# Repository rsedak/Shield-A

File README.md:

Introduction
============

Shield-A is Arduino Uno based shield for student education compatible with BASCOM-AVR(C) and Arduino IDE.
During programming please keep in mind next design rules:
- D0-D7 — LEDs can be used only if D12 is set to OUTPUT HIGH state
- LCD 1602 — can be used only if A3 is set to OUTPUT HIGH state
- RGB LED — are connected in matrix (D5-D7 - colors; D8-D11 - LEDs)
- D12 — enables D0-D7 LEDs
- D13 — reserved for buzzer
- A0 — reserved for potentiometer
- A1,A2 — reserved for switch in INPUT_PULLUP mode
- A3 — enables LCD 1602 back-light
- A4,A5 — reserved for I2C communication with on board pull-up resistors

Contributors
------------
- Petar Jurković — an initial idea for the educational shield with a list of features, QA test.
- Vladimir Mitrović — features, BASCOM-AVR expertise, schematic design
- Robert Sedak — features, Arduino expertise, schematic design, CAD design. 

Application
-----------
Robert Sedak made a video with examples programmed in Arduino IDE:

You can download examples from [here](examples/). 
Examples which name ends with '_R' are solution with register maniputalion.

Bill Of Materials
-----------------
- 1 ea., PCB from [PCBway.com](https://www.pcbway.com/project/shareproject/Shield_A_for_Arduino_Uno.html)
- 9 ea., 1K ohm 1/4W 1% Resistor (R1-R8, R13)
- 2 ea., 100 ohm 1/4W 1% Resistor (R9, R10)
- 2 ea., 560 ohm 1/4W 1% Resistor (R11-R12)
- 4 ea., 10K ohm 1/4W 1% Resistor (R14, R15, R17, R18)
- 2 ea., 18.2 ohm 1/4W 1% Resistor (R16)
- 8 ea., LED 3mm (D0-D7)
- 4 ea., RGB LED 5mm common Katode (D8-D11)
- 1 ea., 14x7.5mm passive electronic piezoelectric buzzer SE
- 2 ea., MOSFET BS170
- 1 ea., 3386-P 10K potentiometer with knob
- 1 ea., RV09 10K potentiometer - long shaft
- 1 ea., 2.54mm pitch slide DIP switch 2-bit
- 1 ea., 6x6x4.3mm SPST Momentary push switch
- 2 ea., 6x6x10mm SPST Momentary push switch
- 1 ea., 1x16Pin 2.54mm Straight Pin Header - Black
- 1 ea., 1x10Pin 2.54mm Straight Pin Header - Black
- 2 ea., 1x8Pin 2.54mm Straight Pin Header - Black
- 1 ea., 1x6Pin 2.54mm Straight Pin Header - Black
- 1 ea., 1x4 pin 2.54mm Socket Connector
- 1 ea., 1x16 pin 2.54mm Socket Connector
- 1 ea., LCD 1602 HD44780 (pin 15 is anode, pin 16 is katode)

Design Files
------------
This project is designed using Open Source [KiCad](http://kicad-pcb.org/). Design files are located in the [design_files](design_files/) folder.  You can see the [schematic](images/shield-a_schematic.png).

Gerber files
------------
You can download gerber files from [here](gerber/shield_a_v1.1.zip).

Firmware
--------
This project can be programmed using the Open Source [Arduino](https://www.arduino.cc/) and [BASCOM-AVR(C)](https://www.mcselec.com/index.php?option=com_content&task=view&id=14&Itemid=103).
Arduino examples are located in [examples](examples/) folder.

Assembly Instructions
---------------------
TBD

License
-------
[Attribution-ShareAlike 4.0 International (CC BY-SA 4.0)](https://creativecommons.org/licenses/by-sa/4.0/)

You are free to:
- Share — copy and redistribute the material in any medium or format
- Adapt — remix, transform, and build upon the material

This license is acceptable for Free Cultural Works.
- The licensor cannot revoke these freedoms as long as you follow the license terms.

Under the following terms:
- Attribution — You must give appropriate credit, provide a link to the license, and indicate if changes were made. You may do so in any reasonable manner, but not in any way that suggests the licensor endorses you or your use.
- ShareAlike — If you remix, transform, or build upon the material, you must distribute your contributions under the same license as the original.

No additional restrictions — You may not apply legal terms or technological measures that legally restrict others from doing anything the license permits.

Reference Designs ARE PROVIDED "AS IS" AND "WITH ALL FAULTS". Authors DISCLAIMS ALL OTHER WARRANTIES, EXPRESS OR IMPLIED, REGARDING PRODUCTS, INCLUDING BUT NOT LIMITED TO, ANY IMPLIED WARRANTIES OF MERCHANTABILITY OR FITNESS FOR A PARTICULAR PURPOSE.
Authors may make changes to specifications and product descriptions at any time, without notice. The Customer must notrely on the absence or characteristics of any features or instructions marked "reserved" or "undefined." 
Authors reservesthese for future definition and shall have no responsibility whatsoever for conflicts or incompatibilities arising from future changes to them. The product information on the Web Site or Materials is subject to change without notice. Do not finalize a design with this info.

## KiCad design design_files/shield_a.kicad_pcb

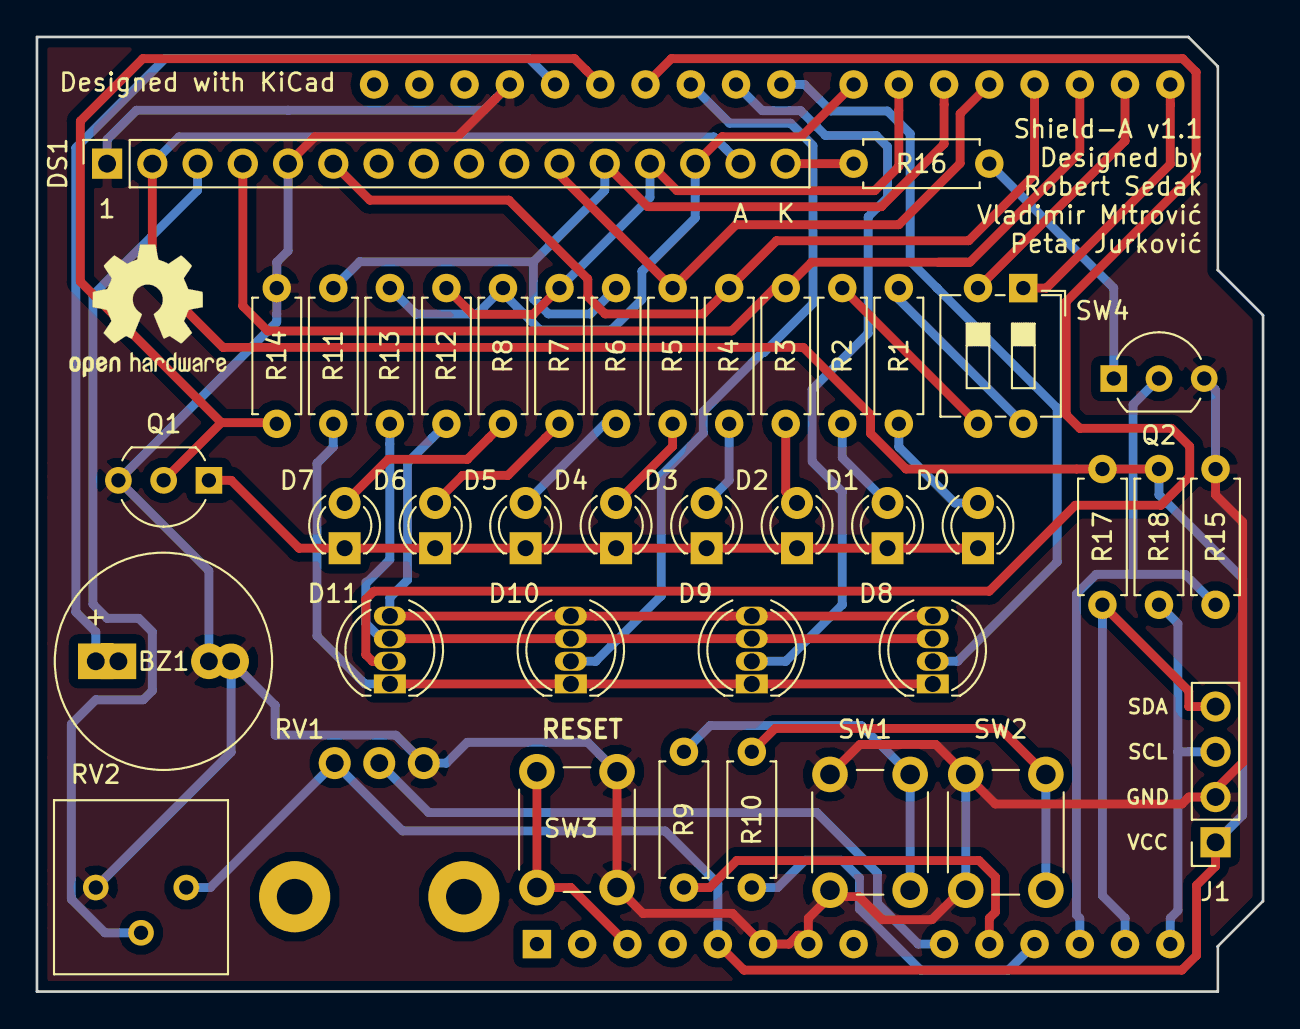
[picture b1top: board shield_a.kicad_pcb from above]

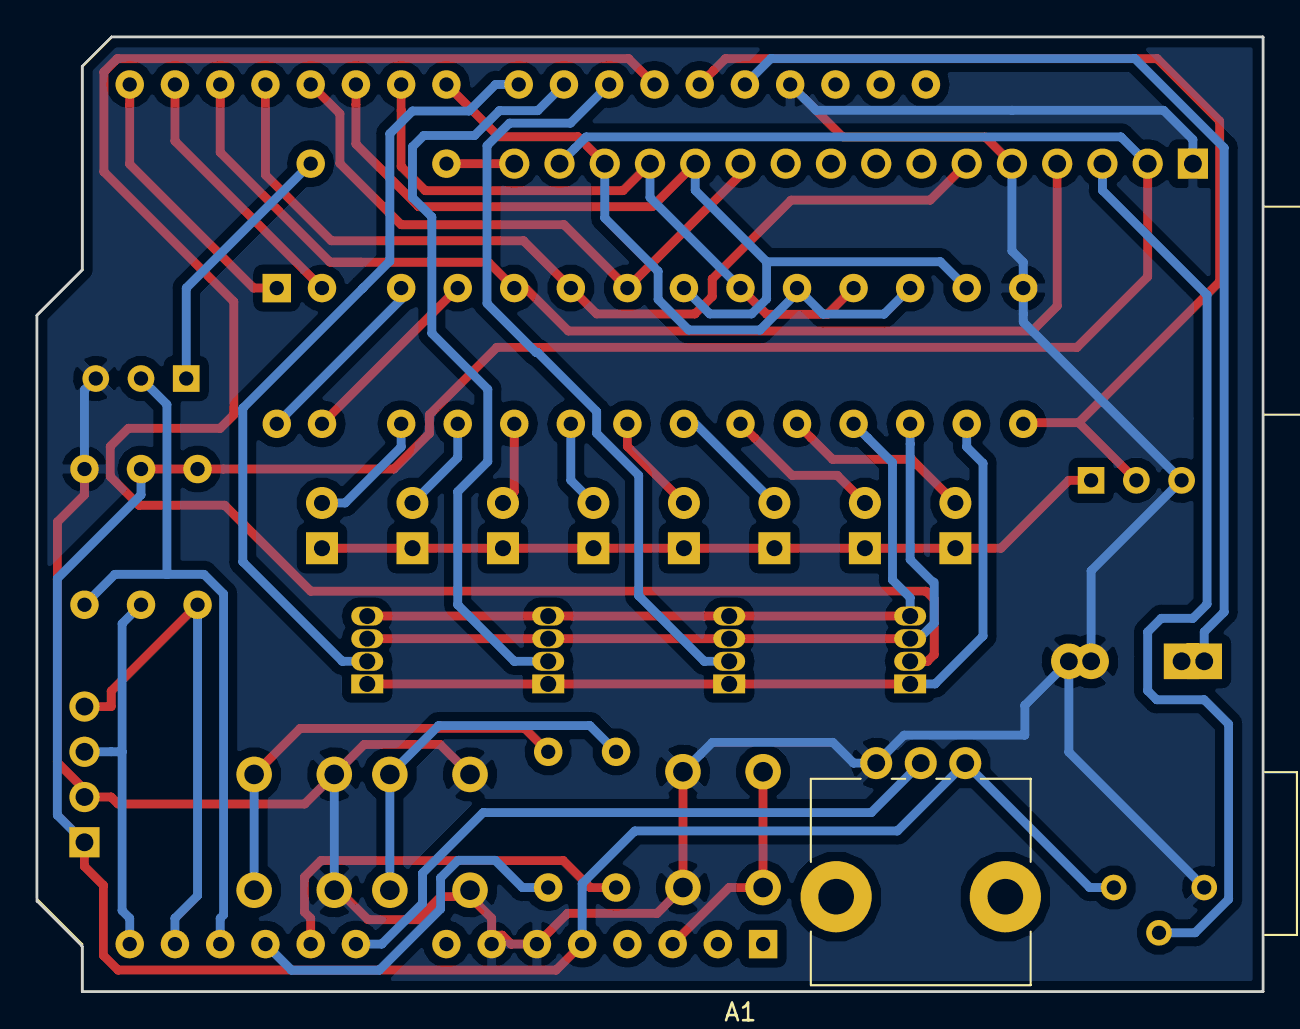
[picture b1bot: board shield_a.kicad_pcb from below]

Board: 2 copper layers, 68.8 x 53.6 mm, 42 parts (2 on the bottom side), 42 nets.

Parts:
A1: Arduino_UNO_R3
BZ1: Buzzer; Buzzer_12x9.5RM7.6_5
D0, D1, D2, D3, D4, D5, D6, D7: 3mm; LED_D3.0mm
D8, D9, D10, D11: LED_RCBG; LED_D5.0mm-4_RGB
DS1: WC1602A; PinSocket_1x16_P2.54mm_Vertical
J1: Conn_01x04_Male; PinSocket_1x04_P2.54mm_Vertical
Q1, Q2: BS170; TO-92_Inline_Wide
R1, R2, R3, R4, R5, R6, R7, R8: 1.5K; R_Axial_DIN0207_L6.3mm_D2.5mm_P7.62mm_Horizontal
R9, R10: 100R; R_Axial_DIN0207_L6.3mm_D2.5mm_P7.62mm_Horizontal
R11, R12, R13: 470; R_Axial_DIN0207_L6.3mm_D2.5mm_P7.62mm_Horizontal
R14, R15: 10k; R_Axial_DIN0207_L6.3mm_D2.5mm_P7.62mm_Horizontal
R16: 18R; R_Axial_DIN0207_L6.3mm_D2.5mm_P7.62mm_Horizontal
R17, R18: 10K; R_Axial_DIN0207_L6.3mm_D2.5mm_P7.62mm_Horizontal
RV1: 10k; Potentiometer_Alps_RK09L_Single_Vertical
RV2: 10k; Potentiometer_Bourns_3386P_Vertical
SW1, SW2, SW3: SW_Push; SW_PUSH_6mm
SW4: SW_DIP_x02; SW_DIP_SPSTx02_Slide_6.7x6.64mm_W7.62mm_P2.54mm_LowProfile

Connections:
+5V: A1.5, DS1.2, DS1.15, J1.1, R17.2, R18.2, RV1.3, RV2.3
A1: R9.1, SW1.1
A2: R10.1, SW2.1
D2: A1.17, DS1.4, R3.1
D3: A1.18, DS1.6, R4.1
D4: A1.19, DS1.11, R5.1
D5: A1.20, DS1.12, R6.1, R11.1
D6: A1.21, DS1.13, R7.1, R12.1
D7: A1.22, DS1.14, R8.1, R13.1
D8: A1.23, D8.2
D9: A1.24, D9.2
D10: A1.25, D10.2
D11: A1.26, D11.2
GND: A1.6, A1.7, A1.29, BZ1.2, DS1.1, DS1.5, J1.2, Q1.3, Q2.3, R14.2, R15.2, RV1.1, RV2.1, SW1.2, SW2.2, SW3.2
unnamed: A1.3, SW3.1
unnamed: A1.9, RV1.2
unnamed: A1.10, R9.2
unnamed: A1.11, R10.2
unnamed: A1.12, Q2.2, R15.1
unnamed: A1.15, SW4.1
unnamed: A1.16, SW4.2
unnamed: A1.27, Q1.2, R14.1
unnamed: A1.28, BZ1.1
unnamed: D0.1, D1.1, D2.1, D3.1, D4.1, D5.1, D6.1, D7.1, Q1.1
unnamed: D0.2, R1.2
unnamed: D1.2, R2.2
unnamed: D2.2, R3.2
unnamed: D3.2, R4.2
unnamed: D4.2, R5.2
unnamed: D5.2, R6.2
unnamed: D6.2, R7.2
unnamed: D7.2, R8.2
unnamed: D8.1, D9.1, D10.1, D11.1, R11.2
unnamed: D8.3, D9.3, D10.3, D11.3, R13.2
unnamed: D8.4, D9.4, D10.4, D11.4, R12.2
unnamed: DS1.3, RV2.2
unnamed: DS1.16, R16.1
unnamed: Q2.1, R16.2
unnamed: R1.1, SW4.4
unnamed: R2.1, SW4.3
SCL: A1.14, J1.3, R18.1
SDA: A1.13, J1.4, R17.1

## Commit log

2019-11-17 changes in README.md file
2023-12-14 Adding schematic in PDF

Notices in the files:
design_files/shield_a.kicad_pcb:
License: CC-BY-SA 3.0
